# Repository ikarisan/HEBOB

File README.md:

# HEVO X-Carriage Breakout Board (HEBOB)

The HEBOB is a simple PCB to connect the hotend carriage of an Hypercube Evolution 3D printer to a Duet3D board. At the moment there are three versions with different connectors you can use:

  - HDMI cable and screw terminals
  - VGA cable and screw terminals
  - VGA cable and JST-XH / screw terminals

## BOM

You will need the following parts.

### HDMI

| Component | Link |
| ------ | ------ |
| J1 | [https://secure.reichelt.de/d-sub-buchse-high-density-15-polig-print-gew-hd-15fw-p8506.html]|
| J2-J4 | 6x RND 205-00233 [https://secure.reichelt.de/loetbare-schraubklemme-3-pol-rm-5-08-mm-90-rnd-205-00233-p170278.html] |

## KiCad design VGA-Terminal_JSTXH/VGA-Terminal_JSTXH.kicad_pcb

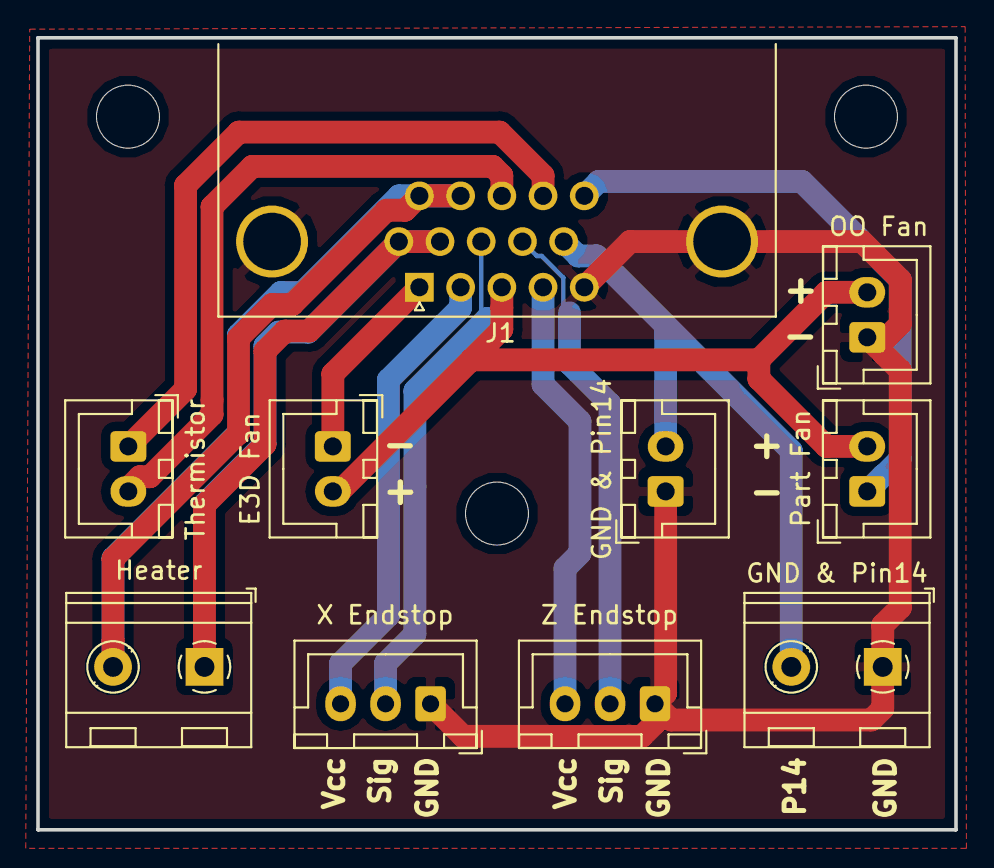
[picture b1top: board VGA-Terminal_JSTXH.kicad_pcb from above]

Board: 2 copper layers, 51.0 x 44.0 mm, 13 parts (0 on the bottom side), 13 nets.

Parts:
H1, H2, H3: MountingHole; MountingHole_3.5mm
J1: DB15_Female_HighDensity_MountingHoles; DSUB-15-HD_Assmann
J2: Thermistor; JST_XH_B02B-XH-A_1x02_P2.50mm_Vertical
J3: Heater; TerminalBlock_RND_205-00232_1x02_P5.08mm_Horizontal
J4: E3D Fan; JST_XH_B02B-XH-A_1x02_P2.50mm_Vertical
J5: X Endstop; JST_XH_B03B-XH-A_1x03_P2.50mm_Vertical
J6: Z Endstop; JST_XH_B03B-XH-A_1x03_P2.50mm_Vertical
J7: GND & Pin14; JST_XH_B02B-XH-A_1x02_P2.50mm_Vertical
J8: Part Fan; JST_XH_B02B-XH-A_1x02_P2.50mm_Vertical
J9: OO Fan; JST_XH_B02B-XH-A_1x02_P2.50mm_Vertical
J10: GND & Pin14; TerminalBlock_RND_205-00232_1x02_P5.08mm_Horizontal

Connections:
E3D_N: J1.1, J4.1
GND: J1.0, J1.5, J5.1, J6.1, J7.1, J9.1, J10.1
HOT_A: J1.11, J1.12, J3.2
HOT_B: J1.6, J1.7, J3.1
Part_N: J1.15, J8.1
Pin14: J1.10, J7.2, J10.2
THERM_A: J1.14, J2.1
THERM_B: J1.13, J2.2
V_FAN: J1.3, J4.2, J8.2, J9.2
Vcc_X: J1.2, J5.3
Vcc_Z: J1.4, J6.3
X_Sig: J1.8, J5.2
Z_Sig: J1.9, J6.2

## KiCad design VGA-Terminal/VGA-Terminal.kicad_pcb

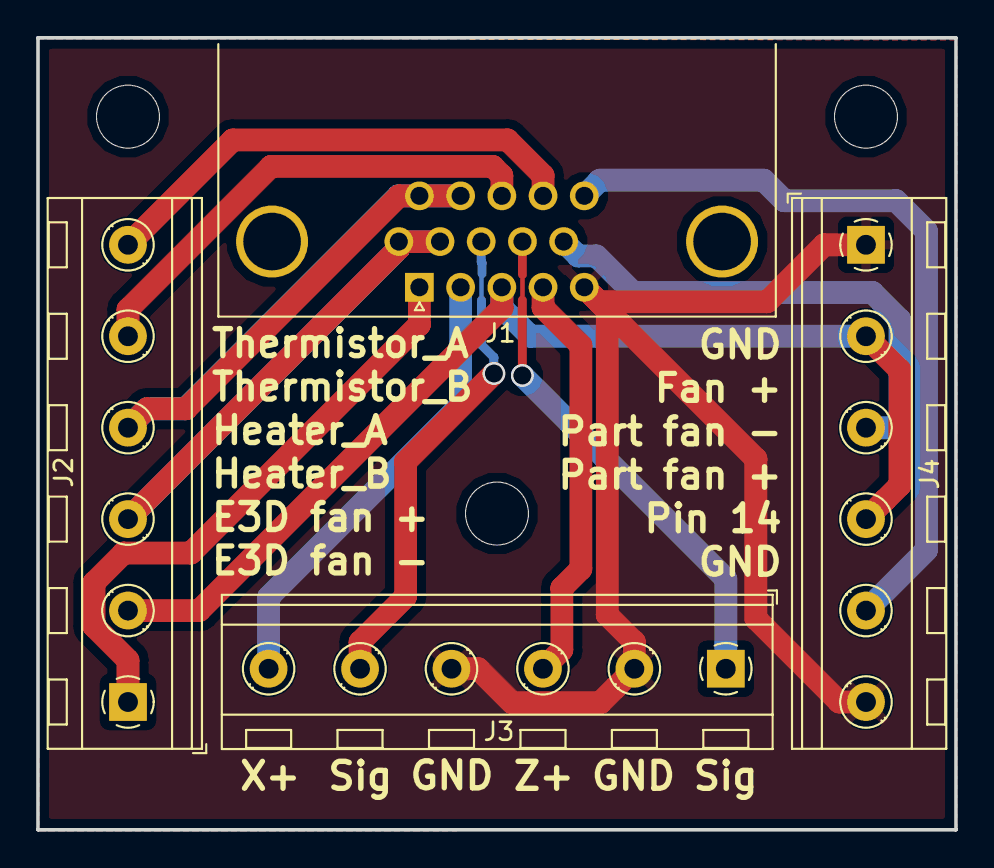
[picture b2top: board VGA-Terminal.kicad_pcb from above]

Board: 2 copper layers, 51.0 x 44.0 mm, 7 parts (0 on the bottom side), 13 nets.

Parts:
H1, H2, H3: MountingHole; MountingHole_3.5mm
J1: DB15_Female_HighDensity_MountingHoles; DSUB-15-HD_Assmann
J2: Hotend; TerminalBlock_RND_205-00236_1x06_P5.08mm_Horizontal
J3: X-Endstop, Fan, Custom; TerminalBlock_RND_205-00236_1x06_P5.08mm_Horizontal
J4: Fan & Custom; TerminalBlock_RND_205-00236_1x06_P5.08mm_Horizontal

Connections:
E3D_N: J1.1, J2.1
GND: J1.5, J3.2, J3.4, J4.1, J4.6
HOT_A: J1.11, J1.12, J2.4
HOT_B: J1.6, J1.7, J2.3
Part_N: J1.10, J4.3
Pin14: J1.15, J4.5
THERM_A: J1.14, J2.6
THERM_B: J1.13, J2.5
V_FAN: J1.3, J2.2, J4.2, J4.4
Vcc_X: J1.2, J3.6
Vcc_Z: J1.4, J3.3
X_Sig: J1.8, J3.5
Z_Sig: J1.9, J3.1

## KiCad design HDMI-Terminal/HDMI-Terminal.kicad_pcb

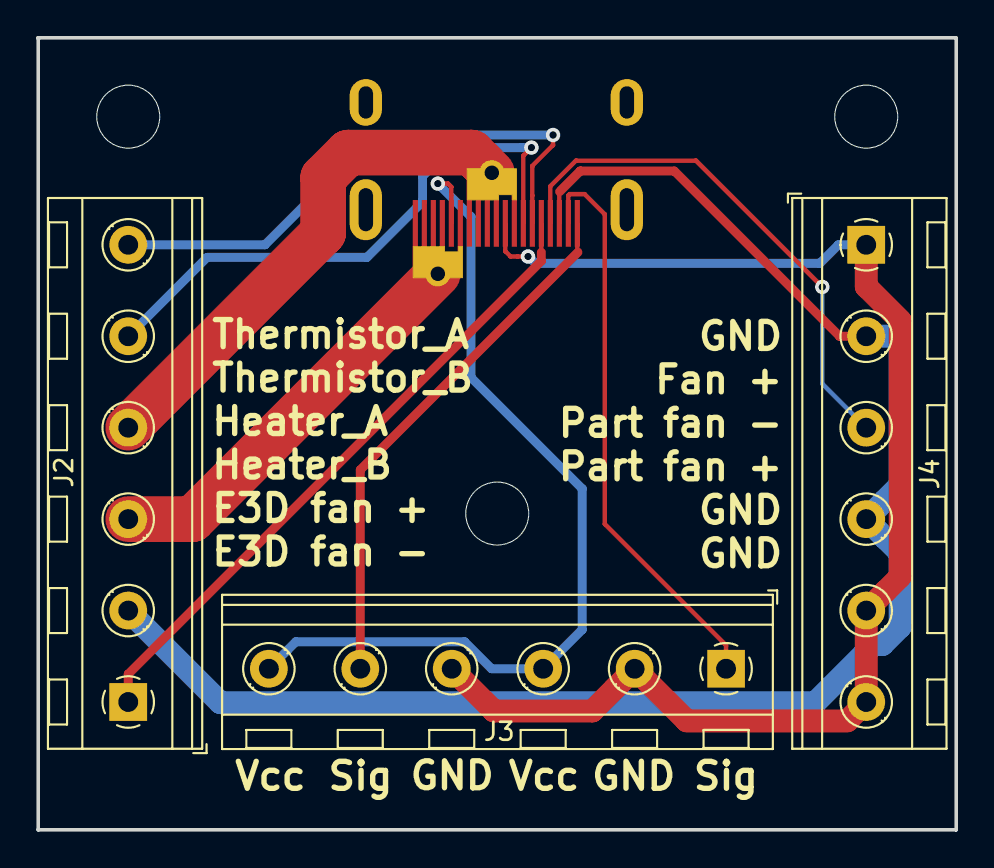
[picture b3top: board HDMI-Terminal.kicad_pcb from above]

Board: 2 copper layers, 51.0 x 44.0 mm, 7 parts (0 on the bottom side), 11 nets.

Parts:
H1, H2, H3: MountingHole; MountingHole_3.5mm
J1: BKL_HDMI_PEB1_HEVO
J2: Hotend; TerminalBlock_RND_205-00236_1x06_P5.08mm_Horizontal
J3: X-Endstop, Fan, Custom; TerminalBlock_RND_205-00236_1x06_P5.08mm_Horizontal
J4: Fan & Custom; TerminalBlock_RND_205-00236_1x06_P5.08mm_Horizontal

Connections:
E3D_N: J1.15, J2.1
GND: J1.11, J3.2, J3.4, J4.1, J4.5, J4.6
HOT_A: J1.7, J2.4
HOT_B: J1.1, J2.3
Part_N: J1.16, J4.3
THERM_A: J1.14, J2.6
THERM_B: J1.13, J2.5
V_FAN: J1.17, J2.2, J4.2, J4.4
Vcc_X: J1.5, J3.3, J3.6
X_Sig: J1.19, J3.5
Z_Sig: J1.18, J3.1

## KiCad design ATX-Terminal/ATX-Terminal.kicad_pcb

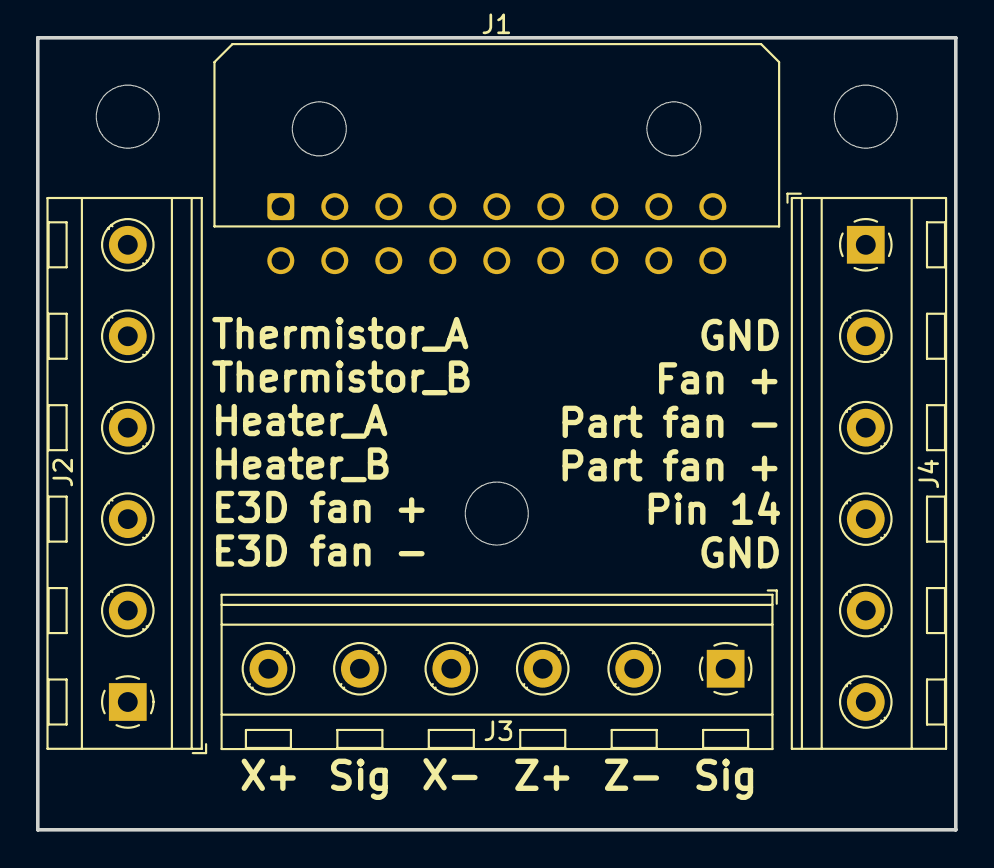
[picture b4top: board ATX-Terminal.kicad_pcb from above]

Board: 2 copper layers, 51.0 x 44.0 mm, 7 parts (0 on the bottom side), 15 nets, no tracks yet.

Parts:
H1, H2, H3: MountingHole; MountingHole_3.5mm
J1: Conn_02x09_Odd_Even; Molex_Micro-Fit_3.0_43045-1800_2x09_P3.00mm_Horizontal
J2: Hotend; TerminalBlock_RND_205-00236_1x06_P5.08mm_Horizontal
J3: X-Endstop, Fan, Custom; TerminalBlock_RND_205-00236_1x06_P5.08mm_Horizontal
J4: Fan & Custom; TerminalBlock_RND_205-00236_1x06_P5.08mm_Horizontal

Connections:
E3D_N: J1.17, J2.1
GND: J1.8, J3.2, J3.4
HOT_A: J1.1, J2.4
HOT_B: J1.2, J2.3
Part_N: J1.15, J4.5
Pin11: J1.11, J4.4
Pin12: J1.12, J4.3
Pin13: J1.13, J4.2
Pin14: J1.14, J4.1
THERM_A: J1.3, J2.6
THERM_B: J1.4, J2.5
V_FAN: J1.18, J2.2, J4.6
Vcc_X: J1.6, J3.6
Vcc_Z: J1.10, J3.3
Z_Sig: J1.9, J3.1

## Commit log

2019-01-25 INIT
2019-02-11 Corrected the footprint
2019-02-11 Added these....
2019-02-11 Deleted deprecated GERBER files
2019-02-13 Breakout with JST-XH connectors
2019-02-14 - Replaced the footprints - Added a additional screw terminal for the custom pin 14
2019-02-22 New README.md
2019-02-22 New SUB-D
